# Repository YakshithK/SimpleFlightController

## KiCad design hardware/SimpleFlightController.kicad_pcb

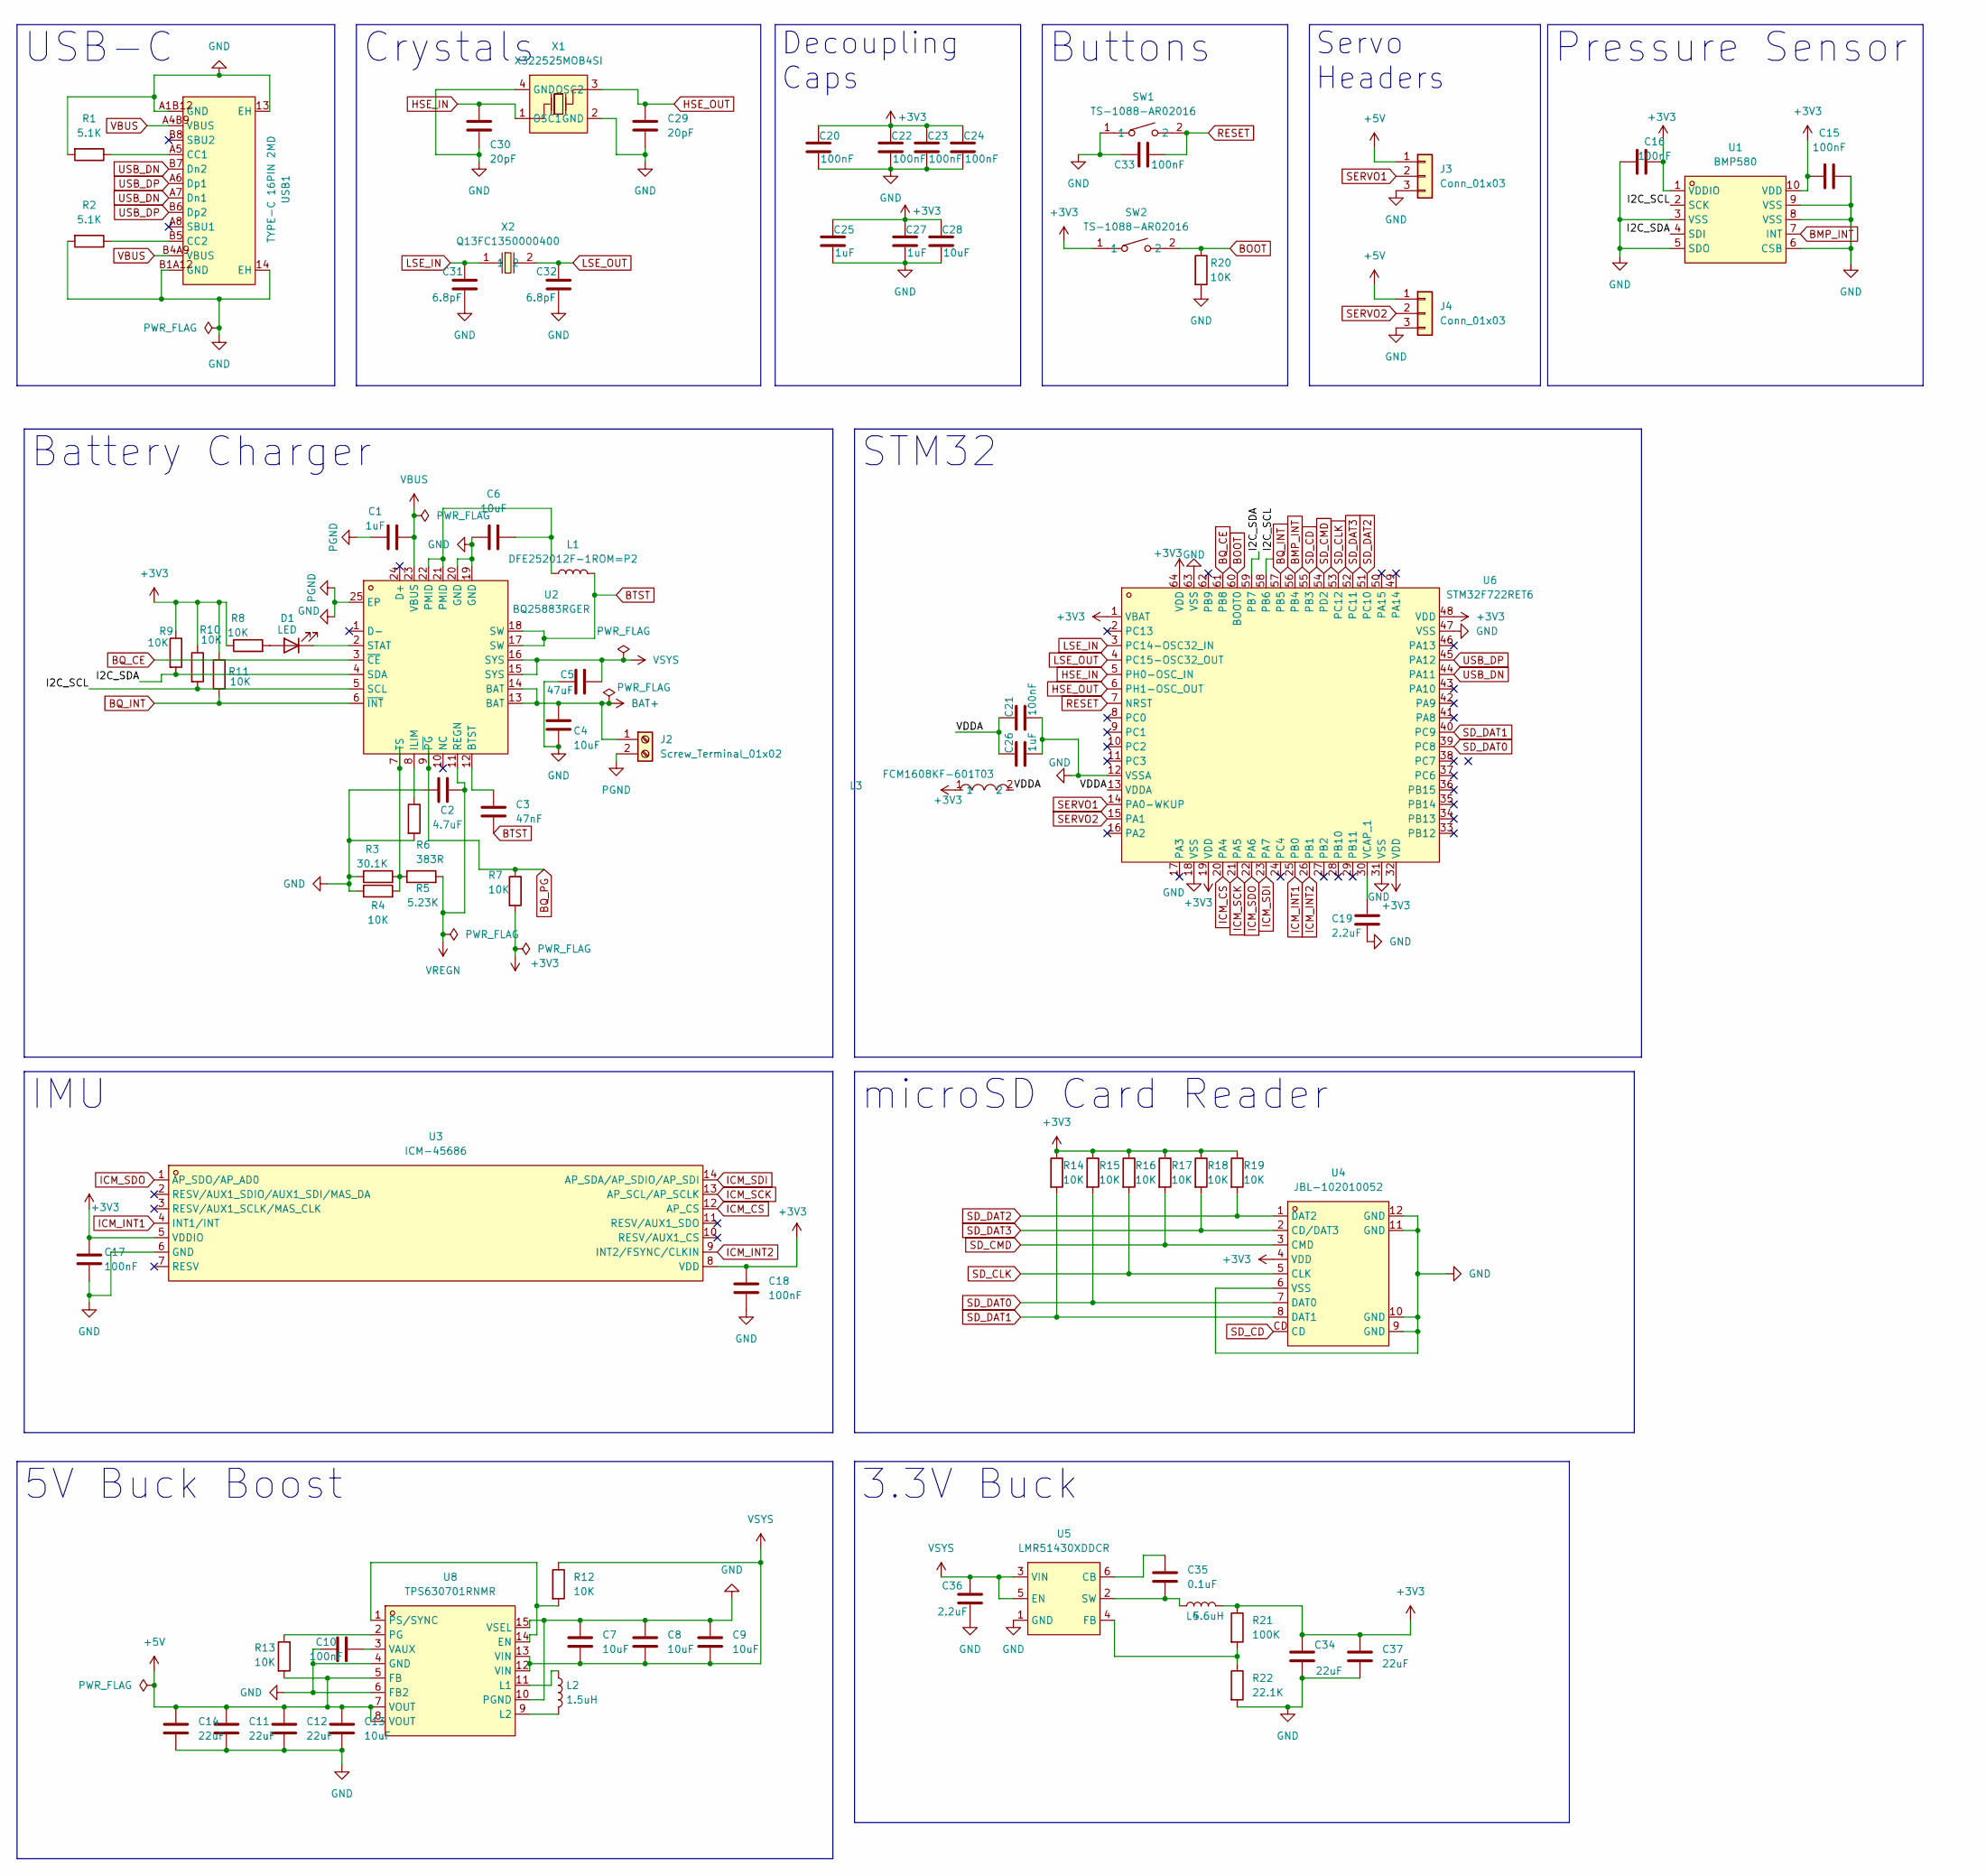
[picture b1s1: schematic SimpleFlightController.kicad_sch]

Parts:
C1, C25, C26, C27: 1uF; C_0402_1005Metric
C2: 4.7uF; C_0402_1005Metric
C3: 47nF; C_0805_2012Metric
C4, C6, C7, C8, C9, C28: 10uF; C_0805_2012Metric
C5: 47uF; C_0805_2012Metric
C10, C15, C16, C17, C18, C20, C21, C22, C23, C24, C33: 100nF; C_0402_1005Metric
C11, C12, C14, C34, C37: 22uF; C_0805_2012Metric
C13: 10uF; C_0402_1005Metric
C19, C36: 2.2uF; C_0402_1005Metric
C29, C30: 20pF; C_0402_1005Metric
C31, C32: 6.8pF; C_0402_1005Metric
C35: 0.1uF; C_0402_1005Metric
D1: LED; LED_0402_1005Metric
J2: Screw_Terminal_01x02; TerminalBlock_Xinya_XY308-2.54-2P_1x02_P2.54mm_Horizontal
J3, J4: Conn_01x03; PinHeader_1x03_P2.54mm_Vertical
L1: DFE252012F-1ROM=P2; L2520
L2: 1.5uH; IND-SMD_L4.0-W4.0-A
L3: FCM1608KF-601T03; L0603; MPN FCM1608KF-601T03; LCSC Part C141723
L4: 5.6uH; IND-SMD_L3.0-W3.0
R1, R2: 5.1K; R_0201_0603Metric
R3: 30.1K; R_0201_0603Metric
R4, R7, R8, R9, R10, R11, R12, R13, R14, R15, R16, R17, R18, R19, R20: 10K; R_0201_0603Metric
R5: 5.23K; R_0201_0603Metric
R6: 383R; R_0201_0603Metric
R21: 100K; R_0402_1005Metric
R22: 22.1K; R_0201_0603Metric
SW1, SW2: TS-1088-AR02016; SW-SMD_L3.9-W3.0-P4.45; MPN TS-1088-AR02016; LCSC Part C720477
U1: BMP580; LGA-10_L2.0-W2.0-P0.50-TL_BMP580; MPN BMP580; LCSC Part C22391138
U2: BQ25883RGER; VFQFPN-24_L4.0-W4.0-P0.50-BL-EP2.8; MPN BQ25883RGER; LCSC Part C544362
U3: ICM-45686; LGA-14_L3.0-W2.5-P0.50-TL; MPN ICM-45686; LCSC Part C22459454
U4: JBL-102010052; TF-CARD-SMD_JBL-102010052; MPN JBL-102010052; LCSC Part C49441431
U5: LMR51430XDDCR; SOT-23-6_L2.9-W1.6-P0.95-LS2.8-BL; MPN LMR51430XDDCR; LCSC Part C5185863
U6: STM32F722RET6; LQFP-64_L10.0-W10.0-P0.50-LS12.0-BL; MPN STM32F722RET6; LCSC Part C118207
U8: TPS630701RNMR; VQFN-HR-15_L3.0-W2.5-P0.50-BL_TPS63070RNMR; MPN TPS630701RNMR; LCSC Part C2876599
USB1: TYPE-C 16PIN 2MD; USB-C-SMD_TYPE-C-16PIN-2MD-073; MPN TYPE-C 16PIN 2MD(073); LCSC Part C2765186
X1: X322525MOB4SI; CRYSTAL-SMD_4P-L3.2-W2.5-BL; MPN X322525MOB4SI; LCSC Part C9006
X2: Q13FC1350000400; FC-135R_L3.2-W1.5; MPN Q13FC13500004; LCSC Part C32346

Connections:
+3V3: C15.1, C16.2, C17.1, C18.1, C20.1, C22.1, C23.1, C24.1, C25.1, C27.1, C28.1, C34.1, C37.1, L3.1, L4.2, R7.2, R8.1, R9.1, R10.1, R11.1, R14.1, R15.1, R16.1, R17.1, R18.1, R19.1, R21.1, SW2.1, U1.1 (VDDIO), U1.10 (VDD), U3.5 (VDDIO), U3.8 (VDD), U4.4 (VDD), U6.1 (VBAT), U6.19 (VDD), U6.32 (VDD), U6.48 (VDD), U6.64 (VDD)
+5V: C11.1, C12.1, C13.1, C14.1, J3.1, J4.1, R13.2, U8.5 (FB), U8.7 (VOUT), U8.8 (VOUT)
/I2C_SCL: R10.2, U1.2 (SCK), U2.5 (SCL), U6.58 (PB6)
/I2C_SDA: R9.2, U1.4 (SDI), U2.4 (SDA), U6.59 (PB7)
/VDDA: C21.1, C26.1, L3.2, U6.13 (VDDA)
BAT+: C4.1, J2.1, U2.13 (BAT), U2.14 (BAT)
BMP_INT: U1.7 (INT), U6.56 (PB4)
BOOT: R20.1, SW2.2, U6.60 (BOOT0)
BQ_CE: U2.3 (~CE), U6.61 (PB8)
BQ_INT: R11.2, U2.6 (~INT), U6.57 (PB5)
BQ_PG: R7.1, U2.9 (~PG)
BTST: C3.2, L1.2, U2.17 (SW), U2.18 (SW)
GND: C1.1, C2.1, C4.2, C5.1, C6.1, C7.1, C8.1, C9.1, C10.1, C11.2, C12.2, C13.2, C14.2, C15.2, C16.1, C17.2, C18.2, C19.2, C20.2, C21.2, C22.2, C23.2, C24.2, C25.2, C26.2, C27.2, C28.2, C29.2, C30.2, C31.2, C32.2, C33.2, C34.2, C36.2, C37.2, J2.2, J3.3, J4.3, R1.2, R2.2, R3.1, R4.1, R6.2, R20.2, R22.2, SW1.1, U1.3 (VSS), U1.5 (SDO), U1.6 (CSB), U1.8 (VSS), U1.9 (VSS), U2.19 (GND), U2.20 (GND), U2.25 (EP), U3.6 (GND), U4.6 (VSS), U4.9 (GND), U4.10 (GND), U4.11 (GND), U4.12 (GND), U5.1 (GND), U6.12 (VSSA), U6.18 (VSS), U6.31 (VSS), U6.47 (VSS), U6.63 (VSS), U8.4 (GND), U8.6 (FB2), U8.10 (PGND), U8.15 (VSEL), USB1.13 (EH), USB1.14 (EH), USB1.A1B12 (GND), USB1.B1A12 (GND), X1.2 (GND), X1.4 (GND)
HSE_IN: C30.1, U6.5 (PH0-OSC_IN), X1.1 (OSC1)
HSE_OUT: C29.1, U6.6 (PH1-OSC_OUT), X1.3 (OSC2)
ICM_CS: U3.12 (AP_CS), U6.20 (PA4)
ICM_INT1: U3.4 (INT1/INT), U6.25 (PB0)
ICM_INT2: U3.9 (INT2/FSYNC/CLKIN), U6.26 (PB1)
ICM_SCK: U3.13 (AP_SCL/AP_SCLK), U6.21 (PA5)
ICM_SDI: U3.14 (AP_SDA/AP_SDIO/AP_SDI), U6.23 (PA7)
ICM_SDO: U3.1 (AP_SDO/AP_AD0), U6.22 (PA6)
LSE_IN: C31.1, U6.3 (PC14-OSC32_IN), X2.1
LSE_OUT: C32.1, U6.4 (PC15-OSC32_OUT), X2.2
unnamed: C6.2, L1.1, U2.21 (PMID), U2.22 (PMID)
unnamed: D1.2 (A), R8.2
unnamed: D1.1 (K), U2.2 (STAT)
unnamed: C3.1, U2.12 (BTST)
unnamed: R6.1, U2.8 (ILIM)
unnamed: R3.2, R4.2, R5.1, U2.7 (TS)
unnamed: C35.1, U5.6 (CB)
unnamed: R21.2, R22.1, U5.4 (FB)
unnamed: C35.2, L4.1, U5.2 (SW)
unnamed: C19.1, U6.30 (VCAP_1)
unnamed: R12.2, U8.1 (PS/SYNC), U8.14 (EN)
unnamed: L2.1, U8.11 (L1)
unnamed: L2.2, U8.9 (L2)
unnamed: R13.1, U8.2 (PG)
unnamed: C10.2, U8.3 (VAUX)
unnamed: R1.1, USB1.A5 (CC1)
unnamed: R2.1, USB1.B5 (CC2)
RESET: C33.1, SW1.2, U6.7 (NRST)
SD_CD: U4.CD, U6.55 (PB3)
SD_CLK: R16.2, U4.5 (CLK), U6.53 (PC12)
SD_CMD: R17.2, U4.3 (CMD), U6.54 (PD2)
SD_DAT0: R15.2, U4.7 (DAT0), U6.39 (PC8)
SD_DAT1: R14.2, U4.8 (DAT1), U6.40 (PC9)
SD_DAT2: R19.2, U4.1 (DAT2), U6.51 (PC10)
SD_DAT3: R18.2, U4.2 (CD/DAT3), U6.52 (PC11)
SERVO1: J3.2, U6.14 (PA0-WKUP)
SERVO2: J4.2, U6.15 (PA1)
USB_DN: U6.44 (PA11), USB1.A7 (Dn1), USB1.B7 (Dn2)
USB_DP: U6.45 (PA12), USB1.A6 (Dp1), USB1.B6 (Dp2)
VBUS: C1.2, U2.23 (VBUS), USB1.A4B9 (VBUS), USB1.B4A9 (VBUS)
VREGN: C2.2, R5.2, U2.11 (REGN)
VSYS: C5.2, C7.2, C8.2, C9.2, C36.1, R12.1, U2.15 (SYS), U2.16 (SYS), U5.3 (VIN), U5.5 (EN), U8.12 (VIN), U8.13 (VIN)

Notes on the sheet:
3.3V Buck
Crystals
STM32
Pressure Sensor
Battery Charger
Servo Headers
microSD Card Reader
Buttons
USB-C
IMU
Decoupling Caps
5V Buck Boost

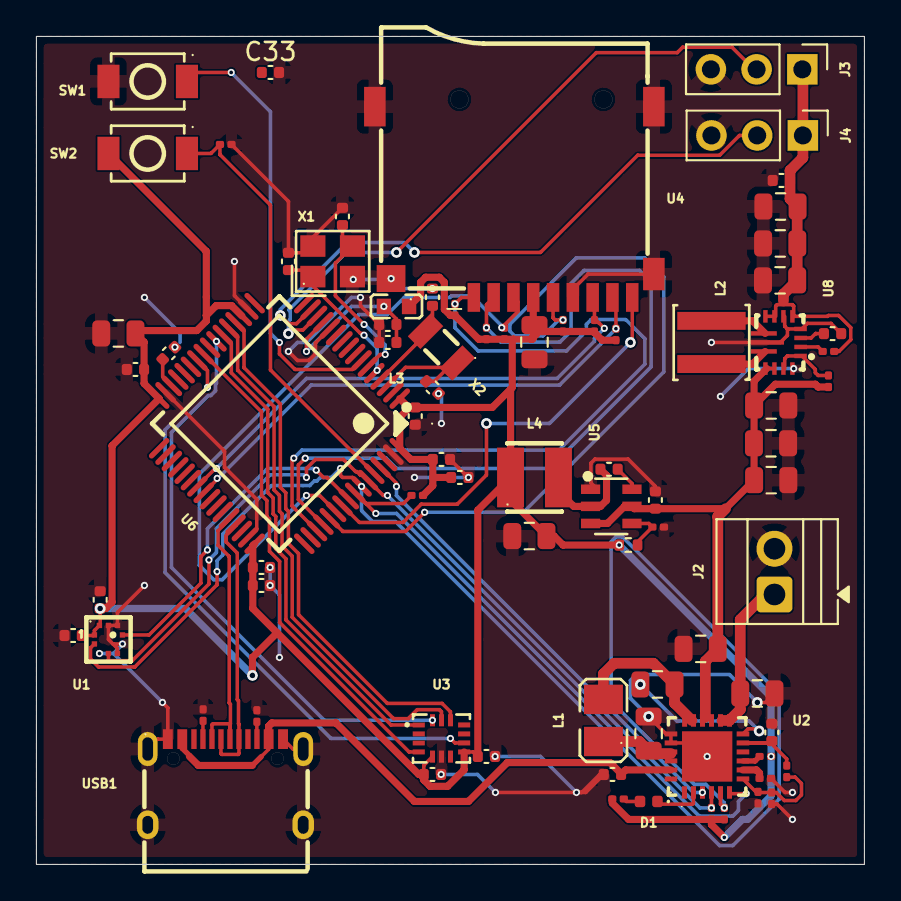
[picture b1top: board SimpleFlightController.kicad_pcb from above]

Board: 2 copper layers, 46.0 x 46.0 mm, 79 parts (0 on the bottom side), 55 nets.

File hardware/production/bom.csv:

Designator,Footprint,Quantity,Value,LCSC Part #
"C1, C25, C26, C27",0402,4,1uF,
"C10, C15, C16, C17, C18, C20, C21, C22, C23, C24, C33",0402,11,100nF,
"C11, C12, C14, C34, C37",0805,5,22uF,
C13,0402,1,10uF,
"C19, C36",0402,2,2.2uF,
C2,0402,1,4.7uF,
"C28, C4, C6, C7, C8, C9",0805,6,10uF,
"C29, C30",0402,2,20pF,
C3,0805,1,47nF,
"C31, C32",0402,2,6.8pF,
C35,0402,1,0.1uF,
C5,0805,1,47uF,
D1,0402,1,LED,
J2,TerminalBlock_Xinya_XY308-2.54-2P_1x02_P2.54mm_Horizontal,1,Screw_Terminal_01x02,
"J3, J4",PinHeader_1x03_P2.54mm_Vertical,2,Conn_01x03,
L1,L2520,1,DFE252012F-1ROM=P2,C435392
L2,IND-SMD_L4.0-W4.0-A,1,1.5uH,C3033018
L3,L0603,1,FCM1608KF-601T03,C141723
L4,IND-SMD_L3.0-W3.0,1,5.6uH,C18236327
"R1, R2",0201,2,5.1K,
"R10, R11, R12, R13, R14, R15, R16, R17, R18, R19, R20, R4, R7, R8, R9",0201,15,10K,
R21,0402,1,100K,
R22,0201,1,22.1K,
R3,0201,1,30.1K,
R5,0201,1,5.23K,
R6,0201,1,383R,
"SW1, SW2",SW-SMD_L3.9-W3.0-P4.45,2,TS-1088-AR02016,C720477
U1,LGA-10_L2.0-W2.0-P0.50-TL_BMP580,1,BMP580,C22391138
U2,VFQFPN-24_L4.0-W4.0-P0.50-BL-EP2.8,1,BQ25883RGER,C544362
U3,LGA-14_L3.0-W2.5-P0.50-TL,1,ICM-45686,C22459454
U4,TF-CARD-SMD_JBL-102010052,1,JBL-102010052,C49441431
U5,SOT-23-6_L2.9-W1.6-P0.95-LS2.8-BL,1,LMR51430XDDCR,C5185863
U6,LQFP-64_L10.0-W10.0-P0.50-LS12.0-BL,1,STM32F722RET6,C118207
U8,VQFN-HR-15_L3.0-W2.5-P0.50-BL_TPS63070RNMR,1,TPS630701RNMR,C2876599
USB1,USB-C-SMD_TYPE-C-16PIN-2MD-073,1,TYPE-C 16PIN 2MD,C2765186
X1,CRYSTAL-SMD_4P-L3.2-W2.5-BL,1,X322525MOB4SI,C9006
X2,FC-135R_L3.2-W1.5,1,Q13FC1350000400,C32346

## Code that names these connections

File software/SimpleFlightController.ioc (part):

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Mcu.Name=STM32F722R(C-E)Tx
Mcu.Package=LQFP64
Mcu.UserName=STM32F722RETx
PA0-WKUP.Signal=S_TIM2_CH1_ETR
PA1.Signal=S_TIM2_CH2
PA11.Mode=Host_Only
PA11.Signal=USB_OTG_FS_DM
PA12.Mode=Host_Only
PA12.Signal=USB_OTG_FS_DP
PA4.Mode=NSS_Signal_Hard_Output
PA4.Signal=SPI1_NSS
PA5.Mode=Full_Duplex_Master
PA5.Signal=SPI1_SCK
PA6.Mode=Full_Duplex_Master
PA6.Signal=SPI1_MISO
PA7.Mode=Full_Duplex_Master
PA7.Signal=SPI1_MOSI
PB0.Signal=GPXTI0
PB1.Signal=GPXTI1
PB3.Signal=GPIO_Input
PB4.Signal=GPXTI4
PB5.Signal=GPXTI5
PB6.Mode=I2C
PB6.Signal=I2C1_SCL
PB7.Mode=I2C
PB7.Signal=I2C1_SDA
PB8.Signal=GPIO_Output
PC10.Mode=SD_4_bits_Wide_bus
PC10.Signal=SDMMC1_D2
PC11.Mode=SD_4_bits_Wide_bus
PC11.Signal=SDMMC1_D3
PC12.Mode=SD_4_bits_Wide_bus
PC12.Signal=SDMMC1_CK
PC14-OSC32_IN.Mode=LSE-External-Oscillator
PC14-OSC32_IN.Signal=RCC_OSC32_IN
PC15-OSC32_OUT.Mode=LSE-External-Oscillator
PC15-OSC32_OUT.Signal=RCC_OSC32_OUT
PC8.Mode=SD_4_bits_Wide_bus
PC8.Signal=SDMMC1_D0
PC9.Mode=SD_4_bits_Wide_bus
PC9.Signal=SDMMC1_D1
PD2.Mode=SD_4_bits_Wide_bus
PD2.Signal=SDMMC1_CMD
PH0-OSC_IN.Mode=HSE-External-Oscillator
PH0-OSC_IN.Signal=RCC_OSC_IN
PH1-OSC_OUT.Mode=HSE-External-Oscillator
PH1-OSC_OUT.Signal=RCC_OSC_OUT
RCC.HSE_VALUE=25000000
board=custom
